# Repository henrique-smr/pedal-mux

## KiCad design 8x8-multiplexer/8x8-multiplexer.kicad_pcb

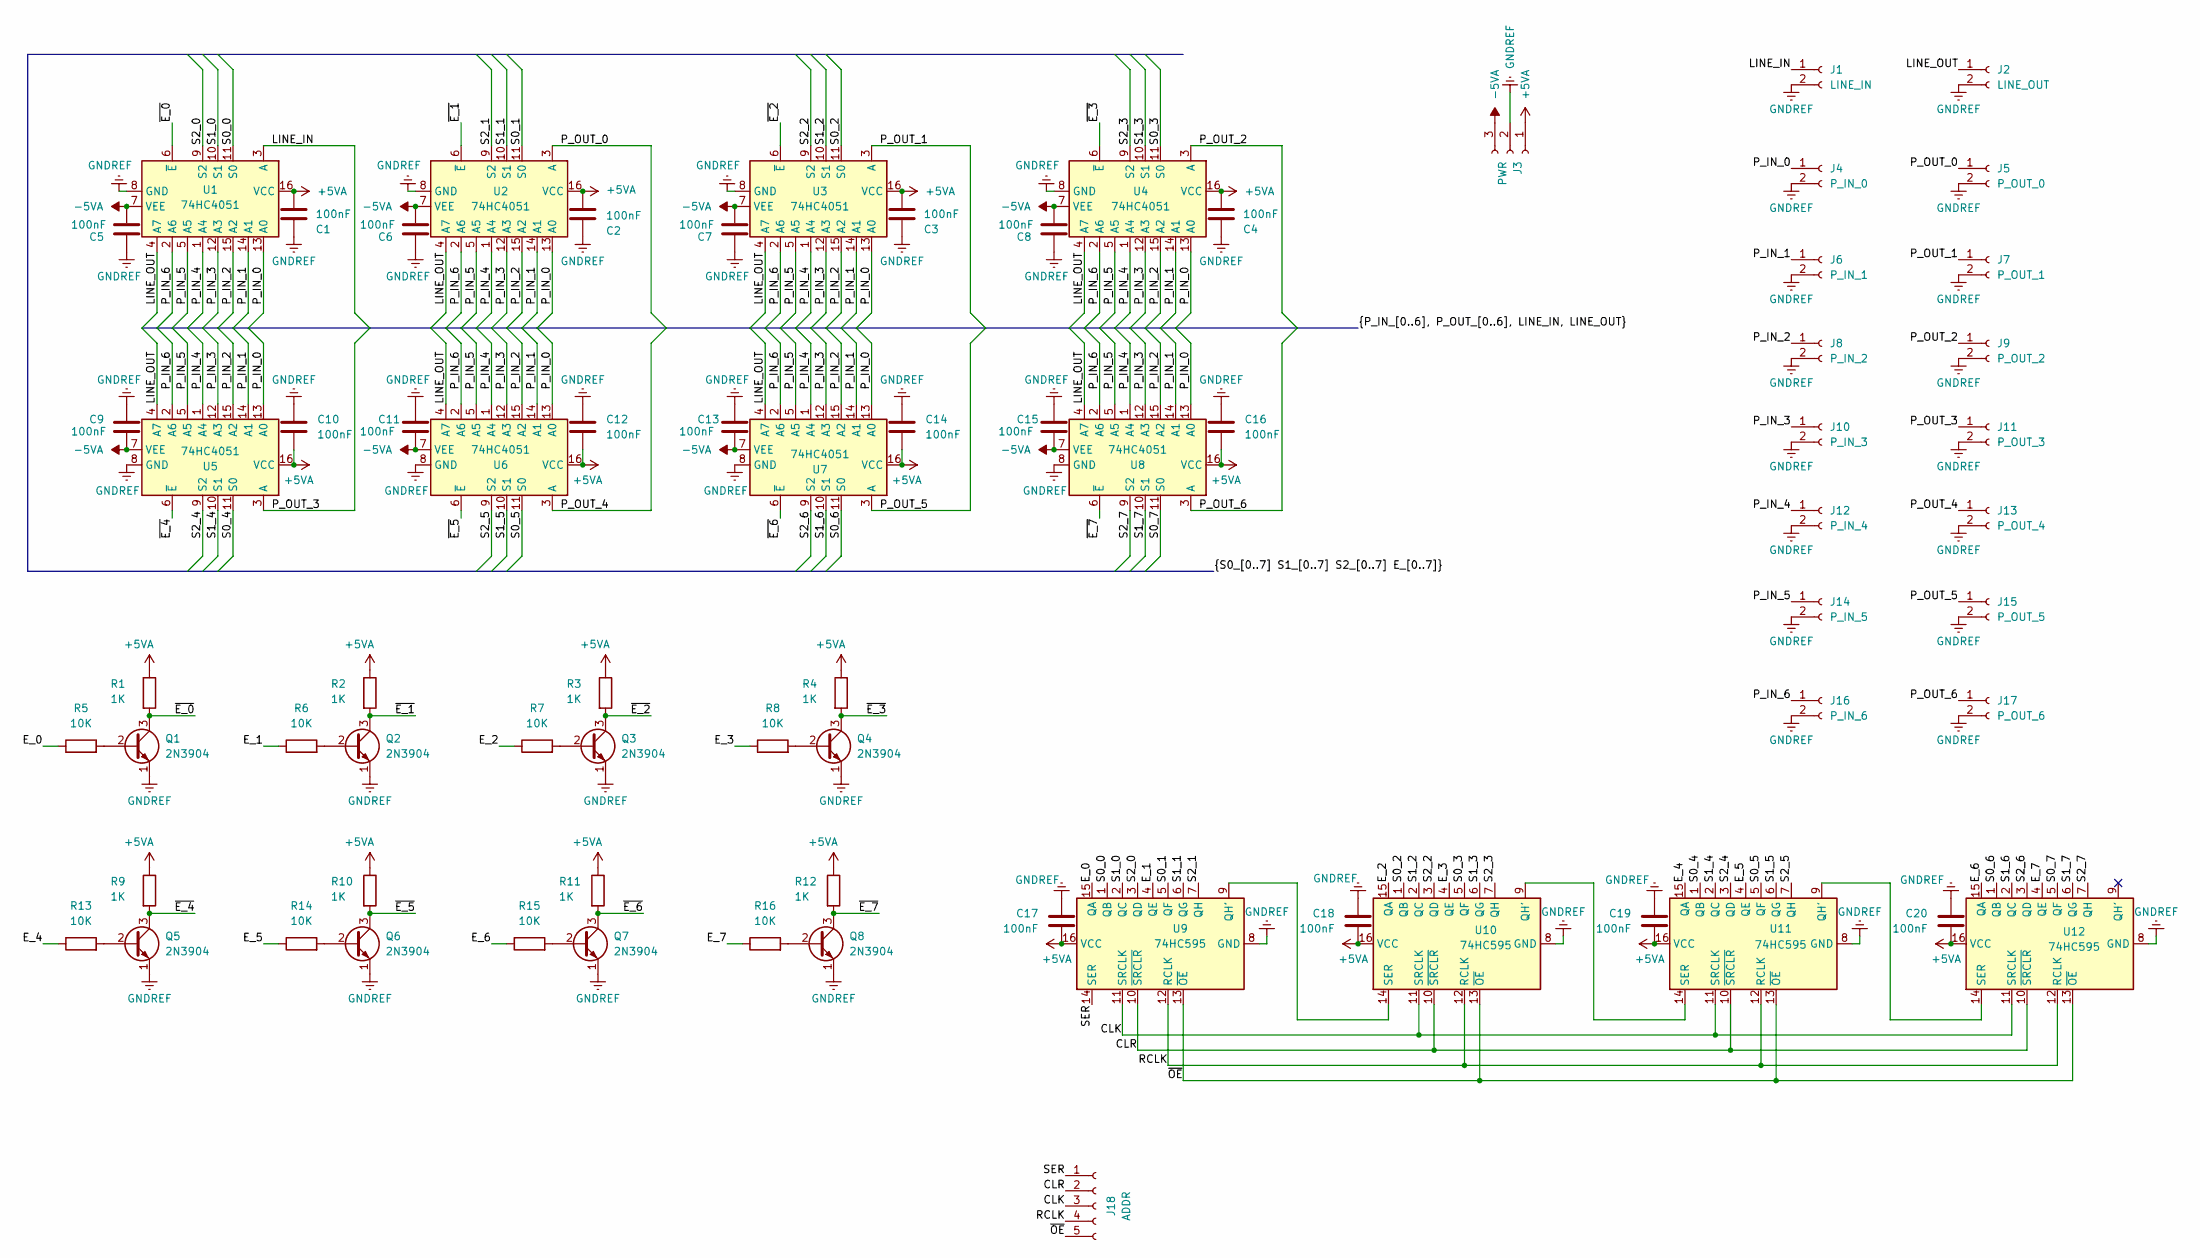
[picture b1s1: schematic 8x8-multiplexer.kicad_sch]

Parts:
C1, C2, C3, C4, C5, C6, C7, C8, C9, C10, C11, C12, C13, C14, C15, C16, C17, C18, C19, C20: 100nF; C_Disc_D4.3mm_W1.9mm_P5.00mm
J1: LINE_IN; PinSocket_1x02_P2.54mm_Vertical
J2: LINE_OUT; PinSocket_1x02_P2.54mm_Vertical
J3: PWR; PinSocket_1x03_P2.54mm_Vertical
J4: P_IN_0; PinSocket_1x02_P2.54mm_Vertical
J5: P_OUT_0; PinSocket_1x02_P2.54mm_Vertical
J6: P_IN_1; PinSocket_1x02_P2.54mm_Vertical
J7: P_OUT_1; PinSocket_1x02_P2.54mm_Vertical
J8: P_IN_2; PinSocket_1x02_P2.54mm_Vertical
J9: P_OUT_2; PinSocket_1x02_P2.54mm_Vertical
J10: P_IN_3; PinSocket_1x02_P2.54mm_Vertical
J11: P_OUT_3; PinSocket_1x02_P2.54mm_Vertical
J12: P_IN_4; PinSocket_1x02_P2.54mm_Vertical
J13: P_OUT_4; PinSocket_1x02_P2.54mm_Vertical
J14: P_IN_5; PinSocket_1x02_P2.54mm_Vertical
J15: P_OUT_5; PinSocket_1x02_P2.54mm_Vertical
J16: P_IN_6; PinSocket_1x02_P2.54mm_Vertical
J17: P_OUT_6; PinSocket_1x02_P2.54mm_Vertical
J18: ADDR; PinSocket_1x05_P2.54mm_Vertical
Q1, Q2, Q3, Q4, Q5, Q6, Q7, Q8: 2N3904; TO-92_Inline_Wide
R1, R2, R3, R4, R9, R10, R11, R12: 1K; R_Axial_DIN0207_L6.3mm_D2.5mm_P7.62mm_Horizontal
R5, R6, R7, R8, R13, R14, R15, R16: 10K; R_Axial_DIN0207_L6.3mm_D2.5mm_P7.62mm_Horizontal
U1, U2, U3, U4, U5, U6, U7, U8: 74HC4051; DIP-16_W7.62mm_LongPads
U9, U10, U11, U12: 74HC595; DIP-16_W7.62mm_LongPads

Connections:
+5VA: C1.2, C2.2, C3.2, C4.2, C10.2, C12.2, C14.2, C16.2, C17.2, C18.2, C19.2, C20.2, J3.1, R1.1, R2.1, R3.1, R4.1, R9.1, R10.1, R11.1, R12.1, U1.16 (VCC), U2.16 (VCC), U3.16 (VCC), U4.16 (VCC), U5.16 (VCC), U6.16 (VCC), U7.16 (VCC), U8.16 (VCC), U9.16 (VCC), U10.16 (VCC), U11.16 (VCC), U12.16 (VCC)
-5VA: C5.2, C6.2, C7.2, C8.2, C9.2, C11.2, C13.2, C15.2, J3.3, U1.7 (VEE), U2.7 (VEE), U3.7 (VEE), U4.7 (VEE), U5.7 (VEE), U6.7 (VEE), U7.7 (VEE), U8.7 (VEE)
/CLK: J18.3, U9.11 (SRCLK), U10.11 (SRCLK), U11.11 (SRCLK), U12.11 (SRCLK)
/CLR: J18.2, U9.10 (~SRCLR), U10.10 (~SRCLR), U11.10 (~SRCLR), U12.10 (~SRCLR)
/E_0: R5.1, U9.15 (QA)
/E_1: R6.1, U9.4 (QE)
/E_2: R7.1, U10.15 (QA)
/E_3: R8.1, U10.4 (QE)
/E_4: R13.1, U11.15 (QA)
/E_5: R14.1, U11.4 (QE)
/E_6: R15.1, U12.15 (QA)
/E_7: R16.1, U12.4 (QE)
/LINE_IN: J1.1, U1.3 (A)
/LINE_OUT: J2.1, U1.4 (A7), U2.4 (A7), U3.4 (A7), U4.4 (A7), U5.4 (A7), U6.4 (A7), U7.4 (A7), U8.4 (A7)
/P_IN_0: J4.1, U1.13 (A0), U2.13 (A0), U3.13 (A0), U4.13 (A0), U5.13 (A0), U6.13 (A0), U7.13 (A0), U8.13 (A0)
/P_IN_1: J6.1, U1.14 (A1), U2.14 (A1), U3.14 (A1), U4.14 (A1), U5.14 (A1), U6.14 (A1), U7.14 (A1), U8.14 (A1)
/P_IN_2: J8.1, U1.15 (A2), U2.15 (A2), U3.15 (A2), U4.15 (A2), U5.15 (A2), U6.15 (A2), U7.15 (A2), U8.15 (A2)
/P_IN_3: J10.1, U1.12 (A3), U2.12 (A3), U3.12 (A3), U4.12 (A3), U5.12 (A3), U6.12 (A3), U7.12 (A3), U8.12 (A3)
/P_IN_4: J12.1, U1.1 (A4), U2.1 (A4), U3.1 (A4), U4.1 (A4), U5.1 (A4), U6.1 (A4), U7.1 (A4), U8.1 (A4)
/P_IN_5: J14.1, U1.5 (A5), U2.5 (A5), U3.5 (A5), U4.5 (A5), U5.5 (A5), U6.5 (A5), U7.5 (A5), U8.5 (A5)
/P_IN_6: J16.1, U1.2 (A6), U2.2 (A6), U3.2 (A6), U4.2 (A6), U5.2 (A6), U6.2 (A6), U7.2 (A6), U8.2 (A6)
/P_OUT_0: J5.1, U2.3 (A)
/P_OUT_1: J7.1, U3.3 (A)
/P_OUT_2: J9.1, U4.3 (A)
/P_OUT_3: J11.1, U5.3 (A)
/P_OUT_4: J13.1, U6.3 (A)
/P_OUT_5: J15.1, U7.3 (A)
/P_OUT_6: J17.1, U8.3 (A)
/RCLK: J18.4, U9.12 (RCLK), U10.12 (RCLK), U11.12 (RCLK), U12.12 (RCLK)
/S0_0: U1.11 (S0), U9.1 (QB)
/S0_1: U2.11 (S0), U9.5 (QF)
/S0_2: U3.11 (S0), U10.1 (QB)
/S0_3: U4.11 (S0), U10.5 (QF)
/S0_4: U5.11 (S0), U11.1 (QB)
/S0_5: U6.11 (S0), U11.5 (QF)
/S0_6: U7.11 (S0), U12.1 (QB)
/S0_7: U8.11 (S0), U12.5 (QF)
/S1_0: U1.10 (S1), U9.2 (QC)
/S1_1: U2.10 (S1), U9.6 (QG)
/S1_2: U3.10 (S1), U10.2 (QC)
/S1_3: U4.10 (S1), U10.6 (QG)
/S1_4: U5.10 (S1), U11.2 (QC)
/S1_5: U6.10 (S1), U11.6 (QG)
/S1_6: U7.10 (S1), U12.2 (QC)
/S1_7: U8.10 (S1), U12.6 (QG)
/S2_0: U1.9 (S2), U9.3 (QD)
/S2_1: U2.9 (S2), U9.7 (QH)
/S2_2: U3.9 (S2), U10.3 (QD)
/S2_3: U4.9 (S2), U10.7 (QH)
/S2_4: U5.9 (S2), U11.3 (QD)
/S2_5: U6.9 (S2), U11.7 (QH)
/S2_6: U7.9 (S2), U12.3 (QD)
/S2_7: U8.9 (S2), U12.7 (QH)
/SER: J18.1, U9.14 (SER)
/~E_0: Q1.3 (C), R1.2, U1.6 (~E)
/~E_1: Q2.3 (C), R2.2, U2.6 (~E)
/~E_2: Q3.3 (C), R3.2, U3.6 (~E)
/~E_3: Q4.3 (C), R4.2, U4.6 (~E)
/~E_4: Q5.3 (C), R9.2, U5.6 (~E)
/~E_5: Q6.3 (C), R10.2, U6.6 (~E)
/~E_6: Q7.3 (C), R11.2, U7.6 (~E)
/~E_7: Q8.3 (C), R12.2, U8.6 (~E)
/~OE: J18.5, U9.13 (~OE), U10.13 (~OE), U11.13 (~OE), U12.13 (~OE)
GNDREF: C1.1, C2.1, C3.1, C4.1, C5.1, C6.1, C7.1, C8.1, C9.1, C10.1, C11.1, C12.1, C13.1, C14.1, C15.1, C16.1, C17.1, C18.1, C19.1, C20.1, J1.2, J2.2, J3.2, J4.2, J5.2, J6.2, J7.2, J8.2, J9.2, J10.2, J11.2, J12.2, J13.2, J14.2, J15.2, J16.2, J17.2, Q1.1 (E), Q2.1 (E), Q3.1 (E), Q4.1 (E), Q5.1 (E), Q6.1 (E), Q7.1 (E), Q8.1 (E), U1.8 (GND), U2.8 (GND), U3.8 (GND), U4.8 (GND), U5.8 (GND), U6.8 (GND), U7.8 (GND), U8.8 (GND), U9.8 (GND), U10.8 (GND), U11.8 (GND), U12.8 (GND)
unnamed: Q1.2 (B), R5.2
unnamed: Q2.2 (B), R6.2
unnamed: Q3.2 (B), R7.2
unnamed: Q4.2 (B), R8.2
unnamed: Q5.2 (B), R13.2
unnamed: Q6.2 (B), R14.2
unnamed: Q7.2 (B), R15.2
unnamed: Q8.2 (B), R16.2
unnamed: U10.9 (QH'), U11.14 (SER)
unnamed: U9.9 (QH'), U10.14 (SER)
unnamed: U11.9 (QH'), U12.14 (SER)

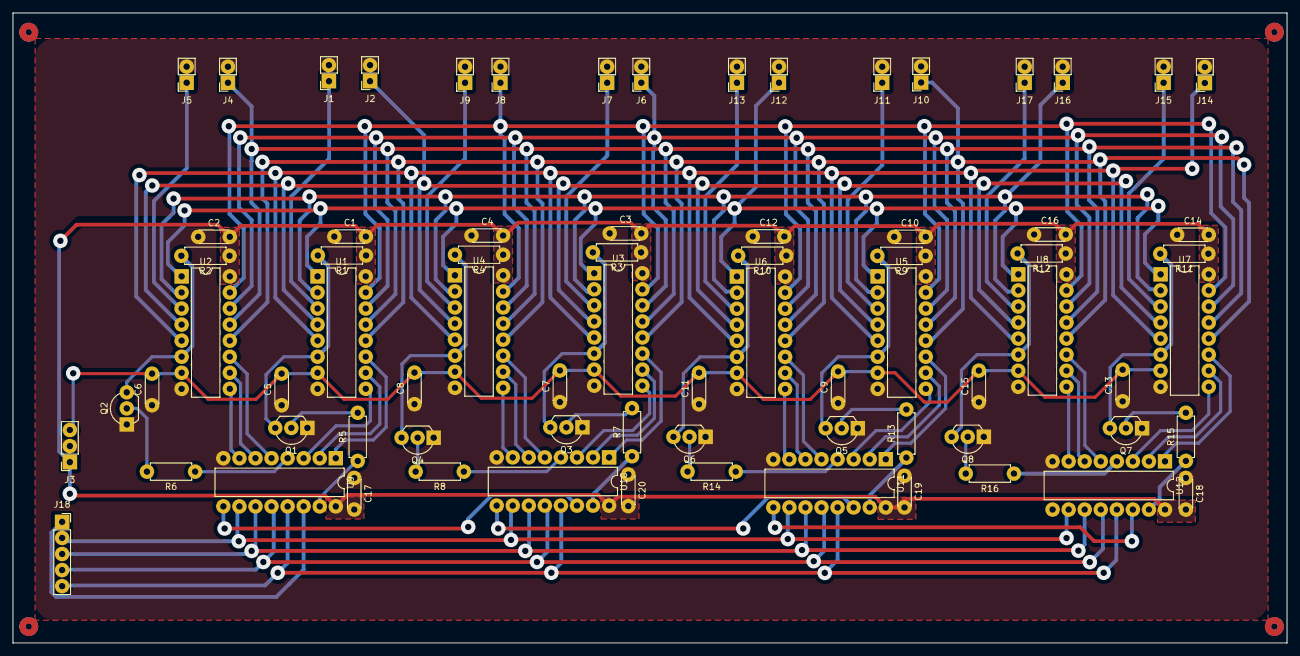
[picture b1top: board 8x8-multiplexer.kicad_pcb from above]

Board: 2 copper layers, 201.5 x 99.6 mm, 74 parts (0 on the bottom side), 75 nets.

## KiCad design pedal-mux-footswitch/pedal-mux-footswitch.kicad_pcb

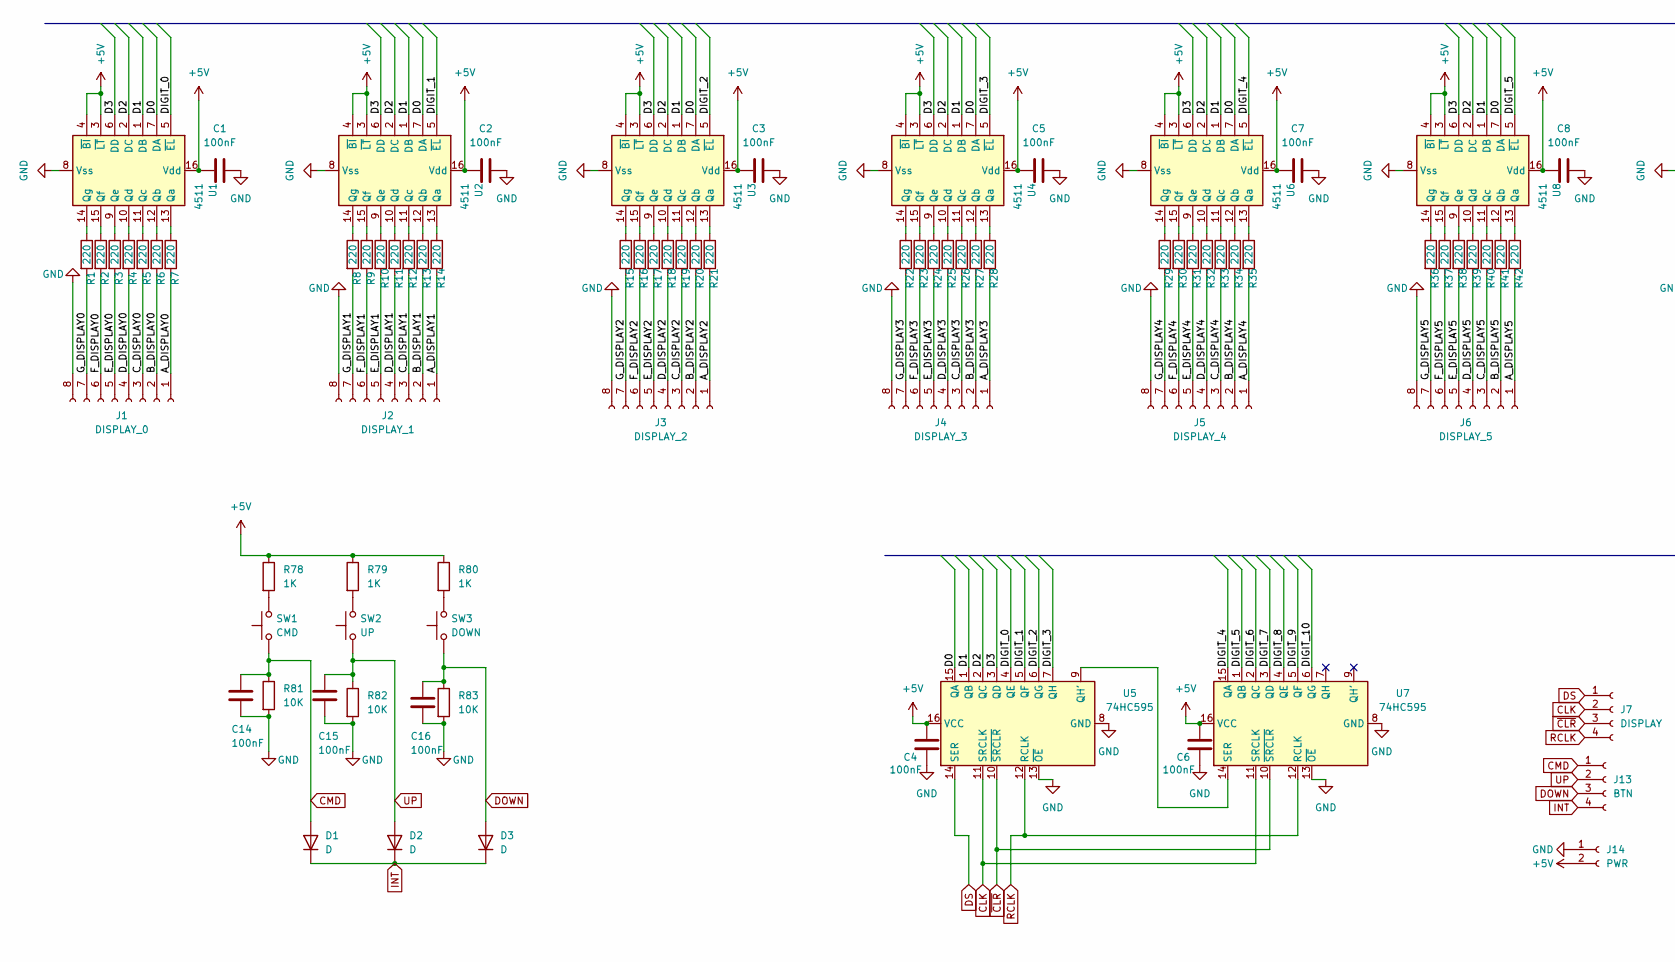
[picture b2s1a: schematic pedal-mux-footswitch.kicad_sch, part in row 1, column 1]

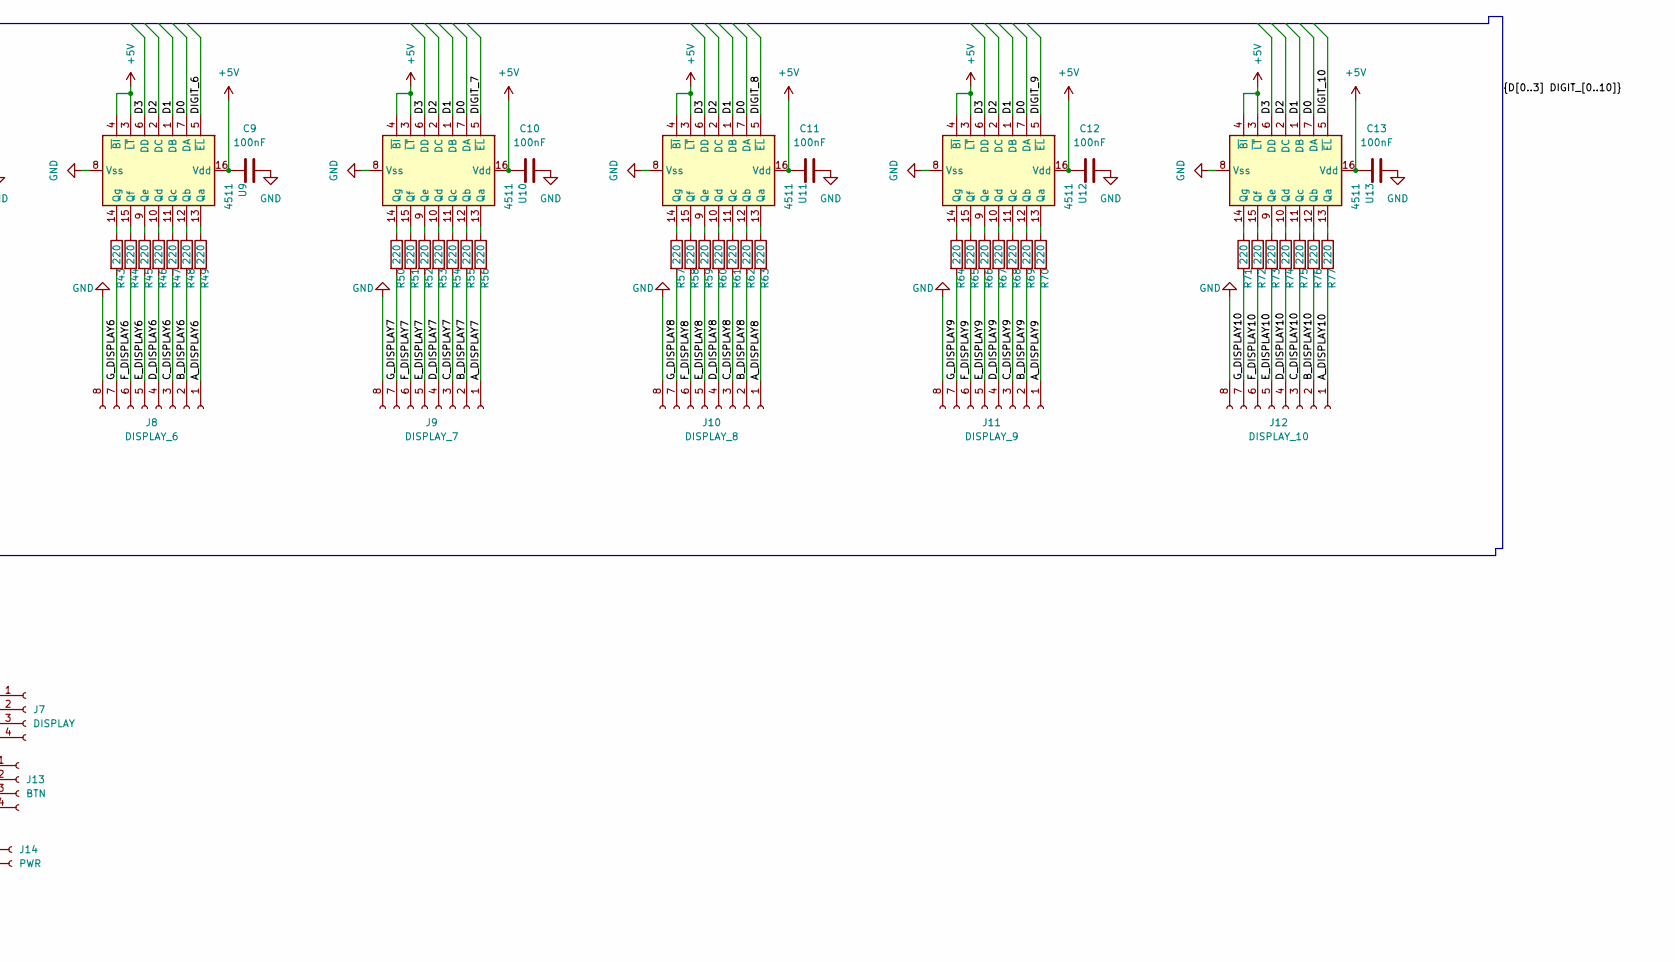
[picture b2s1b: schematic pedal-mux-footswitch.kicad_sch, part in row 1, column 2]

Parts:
C1, C2, C3, C4, C5, C6, C7, C8, C9, C10, C11, C12, C13, C14, C15, C16: 100nF; C_Disc_D5.0mm_W2.5mm_P2.50mm
D1, D2, D3: D; D_DO-41_SOD81_P10.16mm_Horizontal
J1: DISPLAY_0; PinSocket_1x08_P2.54mm_Vertical
J2: DISPLAY_1; PinSocket_1x08_P2.54mm_Vertical
J3: DISPLAY_2; PinSocket_1x08_P2.54mm_Vertical
J4: DISPLAY_3; PinSocket_1x08_P2.54mm_Vertical
J5: DISPLAY_4; PinSocket_1x08_P2.54mm_Vertical
J6: DISPLAY_5; PinSocket_1x08_P2.54mm_Vertical
J7: DISPLAY; PinSocket_1x04_P2.54mm_Vertical
J8: DISPLAY_6; PinSocket_1x08_P2.54mm_Vertical
J9: DISPLAY_7; PinSocket_1x08_P2.54mm_Vertical
J10: DISPLAY_8; PinSocket_1x08_P2.54mm_Vertical
J11: DISPLAY_9; PinSocket_1x08_P2.54mm_Vertical
J12: DISPLAY_10; PinSocket_1x08_P2.54mm_Vertical
J13: BTN; PinSocket_1x04_P2.54mm_Vertical
J14: PWR; PinSocket_1x02_P2.54mm_Vertical
R1, R2, R3, R4, R5, R6, R7, R8, R9, R10, R11, R12, R13, R14, R15, R16, R17, R18, R19, R20, R21, R22, R23, R24, R25, R26, R27, R28, R29, R30, R31, R32, R33, R34, R35, R36, R37, R38, R39, R40, R41, R42, R43, R44, R45, R46, R47, R48, R49, R50, R51, R52, R53, R54, R55, R56, R57, R58, R59, R60, R61, R62, R63, R64, R65, R66, R67, R68, R69, R70, R71, R72, R73, R74, R75, R76, R77: 220; R_Axial_DIN0204_L3.6mm_D1.6mm_P2.54mm_Vertical
R78, R79, R80: 1K; R_Axial_DIN0207_L6.3mm_D2.5mm_P2.54mm_Vertical
R81, R82, R83: 10K; R_Axial_DIN0207_L6.3mm_D2.5mm_P2.54mm_Vertical
SW1: CMD; PinSocket_1x02_P2.54mm_Vertical
SW2: UP; PinSocket_1x02_P2.54mm_Vertical
SW3: DOWN; PinSocket_1x02_P2.54mm_Vertical
U1, U2, U3, U4, U6, U8, U9, U10, U11, U12, U13: 4511; DIP-16_W7.62mm
U5, U7: 74HC595; DIP-16_W7.62mm

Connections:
+5V: C1.1, C2.1, C3.1, C4.1, C5.1, C6.1, C7.1, C8.1, C9.1, C10.1, C11.1, C12.1, C13.1, J14.2, R78.1, R79.1, R80.1, U1.3 (~LT), U1.4 (~BI), U1.16 (Vdd), U2.3 (~LT), U2.4 (~BI), U2.16 (Vdd), U3.3 (~LT), U3.4 (~BI), U3.16 (Vdd), U4.3 (~LT), U4.4 (~BI), U4.16 (Vdd), U5.16 (VCC), U6.3 (~LT), U6.4 (~BI), U6.16 (Vdd), U7.16 (VCC), U8.3 (~LT), U8.4 (~BI), U8.16 (Vdd), U9.3 (~LT), U9.4 (~BI), U9.16 (Vdd), U10.3 (~LT), U10.4 (~BI), U10.16 (Vdd), U11.3 (~LT), U11.4 (~BI), U11.16 (Vdd), U12.3 (~LT), U12.4 (~BI), U12.16 (Vdd), U13.3 (~LT), U13.4 (~BI), U13.16 (Vdd)
/A_DISPLAY0: J1.1, R7.2
/A_DISPLAY1: J2.1, R14.2
/A_DISPLAY2: J3.1, R21.2
/A_DISPLAY3: J4.1, R28.2
/A_DISPLAY4: J5.1, R35.2
/A_DISPLAY5: J6.1, R42.2
/A_DISPLAY6: J8.1, R49.2
/A_DISPLAY7: J9.1, R56.2
/A_DISPLAY8: J10.1, R63.2
/A_DISPLAY9: J11.1, R70.2
/A_DISPLAY10: J12.1, R77.2
/B_DISPLAY0: J1.2, R6.2
/B_DISPLAY1: J2.2, R13.2
/B_DISPLAY2: J3.2, R20.2
/B_DISPLAY3: J4.2, R27.2
/B_DISPLAY4: J5.2, R34.2
/B_DISPLAY5: J6.2, R41.2
/B_DISPLAY6: J8.2, R48.2
/B_DISPLAY7: J9.2, R55.2
/B_DISPLAY8: J10.2, R62.2
/B_DISPLAY9: J11.2, R69.2
/B_DISPLAY10: J12.2, R76.2
/C_DISPLAY0: J1.3, R5.2
/C_DISPLAY1: J2.3, R12.2
/C_DISPLAY2: J3.3, R19.2
/C_DISPLAY3: J4.3, R26.2
/C_DISPLAY4: J5.3, R33.2
/C_DISPLAY5: J6.3, R40.2
/C_DISPLAY6: J8.3, R47.2
/C_DISPLAY7: J9.3, R54.2
/C_DISPLAY8: J10.3, R61.2
/C_DISPLAY9: J11.3, R68.2
/C_DISPLAY10: J12.3, R75.2
/D0: U1.7 (DA), U2.7 (DA), U3.7 (DA), U4.7 (DA), U5.15 (QA), U6.7 (DA), U8.7 (DA), U9.7 (DA), U10.7 (DA), U11.7 (DA), U12.7 (DA), U13.7 (DA)
/D1: U1.1 (DB), U2.1 (DB), U3.1 (DB), U4.1 (DB), U5.1 (QB), U6.1 (DB), U8.1 (DB), U9.1 (DB), U10.1 (DB), U11.1 (DB), U12.1 (DB), U13.1 (DB)
/D2: U1.2 (DC), U2.2 (DC), U3.2 (DC), U4.2 (DC), U5.2 (QC), U6.2 (DC), U8.2 (DC), U9.2 (DC), U10.2 (DC), U11.2 (DC), U12.2 (DC), U13.2 (DC)
/D3: U1.6 (DD), U2.6 (DD), U3.6 (DD), U4.6 (DD), U5.3 (QD), U6.6 (DD), U8.6 (DD), U9.6 (DD), U10.6 (DD), U11.6 (DD), U12.6 (DD), U13.6 (DD)
/DIGIT_0: U1.5 (~EL), U5.4 (QE)
/DIGIT_1: U2.5 (~EL), U5.5 (QF)
/DIGIT_2: U3.5 (~EL), U5.6 (QG)
/DIGIT_3: U4.5 (~EL), U5.7 (QH)
/DIGIT_4: U6.5 (~EL), U7.15 (QA)
/DIGIT_5: U7.1 (QB), U8.5 (~EL)
/DIGIT_6: U7.2 (QC), U9.5 (~EL)
/DIGIT_7: U7.3 (QD), U10.5 (~EL)
/DIGIT_8: U7.4 (QE), U11.5 (~EL)
/DIGIT_9: U7.5 (QF), U12.5 (~EL)
/DIGIT_10: U7.6 (QG), U13.5 (~EL)
/D_DISPLAY0: J1.4, R4.2
/D_DISPLAY1: J2.4, R11.2
/D_DISPLAY2: J3.4, R18.2
/D_DISPLAY3: J4.4, R25.2
/D_DISPLAY4: J5.4, R32.2
/D_DISPLAY5: J6.4, R39.2
/D_DISPLAY6: J8.4, R46.2
/D_DISPLAY7: J9.4, R53.2
/D_DISPLAY8: J10.4, R60.2
/D_DISPLAY9: J11.4, R67.2
/D_DISPLAY10: J12.4, R74.2
/E_DISPLAY0: J1.5, R3.2
/E_DISPLAY1: J2.5, R10.2
/E_DISPLAY2: J3.5, R17.2
/E_DISPLAY3: J4.5, R24.2
/E_DISPLAY4: J5.5, R31.2
/E_DISPLAY5: J6.5, R38.2
/E_DISPLAY6: J8.5, R45.2
/E_DISPLAY7: J9.5, R52.2
/E_DISPLAY8: J10.5, R59.2
/E_DISPLAY9: J11.5, R66.2
/E_DISPLAY10: J12.5, R73.2
/F_DISPLAY0: J1.6, R2.2
/F_DISPLAY1: J2.6, R9.2
/F_DISPLAY2: J3.6, R16.2
/F_DISPLAY3: J4.6, R23.2
/F_DISPLAY4: J5.6, R30.2
/F_DISPLAY5: J6.6, R37.2
/F_DISPLAY6: J8.6, R44.2
/F_DISPLAY7: J9.6, R51.2
/F_DISPLAY8: J10.6, R58.2
/F_DISPLAY9: J11.6, R65.2
/F_DISPLAY10: J12.6, R72.2
/G_DISPLAY0: J1.7, R1.2
/G_DISPLAY1: J2.7, R8.2
/G_DISPLAY2: J3.7, R15.2
/G_DISPLAY3: J4.7, R22.2
/G_DISPLAY4: J5.7, R29.2
/G_DISPLAY5: J6.7, R36.2
/G_DISPLAY6: J8.7, R43.2
/G_DISPLAY7: J9.7, R50.2
/G_DISPLAY8: J10.7, R57.2
/G_DISPLAY9: J11.7, R64.2
/G_DISPLAY10: J12.7, R71.2
CLK: J7.2, U5.11 (SRCLK), U7.11 (SRCLK)
CMD: C14.1, D1.2 (A), J13.1, R81.1, SW1.1
DOWN: C16.1, D3.2 (A), J13.3, R83.1, SW3.1
DS: J7.1, U5.14 (SER)
GND: C1.2, C2.2, C3.2, C4.2, C5.2, C6.2, C7.2, C8.2, C9.2, C10.2, C11.2, C12.2, C13.2, C14.2, C15.2, C16.2, J1.8, J2.8, J3.8, J4.8, J5.8, J6.8, J8.8, J9.8, J10.8, J11.8, J12.8, J14.1, R81.2, R82.2, R83.2, U1.8 (Vss), U2.8 (Vss), U3.8 (Vss), U4.8 (Vss), U5.8 (GND), U5.13 (~OE), U6.8 (Vss), U7.8 (GND), U7.13 (~OE), U8.8 (Vss), U9.8 (Vss), U10.8 (Vss), U11.8 (Vss), U12.8 (Vss), U13.8 (Vss)
INT: D1.1 (K), D2.1 (K), D3.1 (K), J13.4
unnamed: R78.2, SW1.2
unnamed: R79.2, SW2.2
unnamed: R80.2, SW3.2
unnamed: R7.1, U1.13 (Qa)
unnamed: R6.1, U1.12 (Qb)
unnamed: R5.1, U1.11 (Qc)
unnamed: R4.1, U1.10 (Qd)
unnamed: R3.1, U1.9 (Qe)
unnamed: R2.1, U1.15 (Qf)
unnamed: R1.1, U1.14 (Qg)
unnamed: R14.1, U2.13 (Qa)
unnamed: R13.1, U2.12 (Qb)
unnamed: R12.1, U2.11 (Qc)
unnamed: R11.1, U2.10 (Qd)
unnamed: R10.1, U2.9 (Qe)
unnamed: R9.1, U2.15 (Qf)
unnamed: R8.1, U2.14 (Qg)
unnamed: R21.1, U3.13 (Qa)
unnamed: R20.1, U3.12 (Qb)
unnamed: R19.1, U3.11 (Qc)
unnamed: R18.1, U3.10 (Qd)
unnamed: R17.1, U3.9 (Qe)
unnamed: R16.1, U3.15 (Qf)
unnamed: R15.1, U3.14 (Qg)
unnamed: R28.1, U4.13 (Qa)
unnamed: R27.1, U4.12 (Qb)
unnamed: R26.1, U4.11 (Qc)
unnamed: R25.1, U4.10 (Qd)
unnamed: R24.1, U4.9 (Qe)
unnamed: R23.1, U4.15 (Qf)
unnamed: R22.1, U4.14 (Qg)
unnamed: U5.9 (QH'), U7.14 (SER)
unnamed: R35.1, U6.13 (Qa)
unnamed: R34.1, U6.12 (Qb)
unnamed: R33.1, U6.11 (Qc)
unnamed: R32.1, U6.10 (Qd)
unnamed: R31.1, U6.9 (Qe)
unnamed: R30.1, U6.15 (Qf)
unnamed: R29.1, U6.14 (Qg)
unnamed: R42.1, U8.13 (Qa)
unnamed: R41.1, U8.12 (Qb)
unnamed: R40.1, U8.11 (Qc)
unnamed: R39.1, U8.10 (Qd)
unnamed: R38.1, U8.9 (Qe)
unnamed: R37.1, U8.15 (Qf)
unnamed: R36.1, U8.14 (Qg)
unnamed: R49.1, U9.13 (Qa)
unnamed: R48.1, U9.12 (Qb)
unnamed: R47.1, U9.11 (Qc)
unnamed: R46.1, U9.10 (Qd)
unnamed: R45.1, U9.9 (Qe)
unnamed: R44.1, U9.15 (Qf)
unnamed: R43.1, U9.14 (Qg)
unnamed: R56.1, U10.13 (Qa)
unnamed: R55.1, U10.12 (Qb)
unnamed: R54.1, U10.11 (Qc)
unnamed: R53.1, U10.10 (Qd)
unnamed: R52.1, U10.9 (Qe)
unnamed: R51.1, U10.15 (Qf)
unnamed: R50.1, U10.14 (Qg)
unnamed: R63.1, U11.13 (Qa)
unnamed: R62.1, U11.12 (Qb)
unnamed: R61.1, U11.11 (Qc)
unnamed: R60.1, U11.10 (Qd)
unnamed: R59.1, U11.9 (Qe)
unnamed: R58.1, U11.15 (Qf)
unnamed: R57.1, U11.14 (Qg)
unnamed: R70.1, U12.13 (Qa)
unnamed: R69.1, U12.12 (Qb)
unnamed: R68.1, U12.11 (Qc)
unnamed: R67.1, U12.10 (Qd)
unnamed: R66.1, U12.9 (Qe)
unnamed: R65.1, U12.15 (Qf)
unnamed: R64.1, U12.14 (Qg)
unnamed: R77.1, U13.13 (Qa)
unnamed: R76.1, U13.12 (Qb)
unnamed: R75.1, U13.11 (Qc)
unnamed: R74.1, U13.10 (Qd)
unnamed: R73.1, U13.9 (Qe)
unnamed: R72.1, U13.15 (Qf)
unnamed: R71.1, U13.14 (Qg)
RCLK: J7.4, U5.12 (RCLK), U7.12 (RCLK)
UP: C15.1, D2.2 (A), J13.2, R82.1, SW2.1
~CLR: J7.3, U5.10 (~SRCLR), U7.10 (~SRCLR)

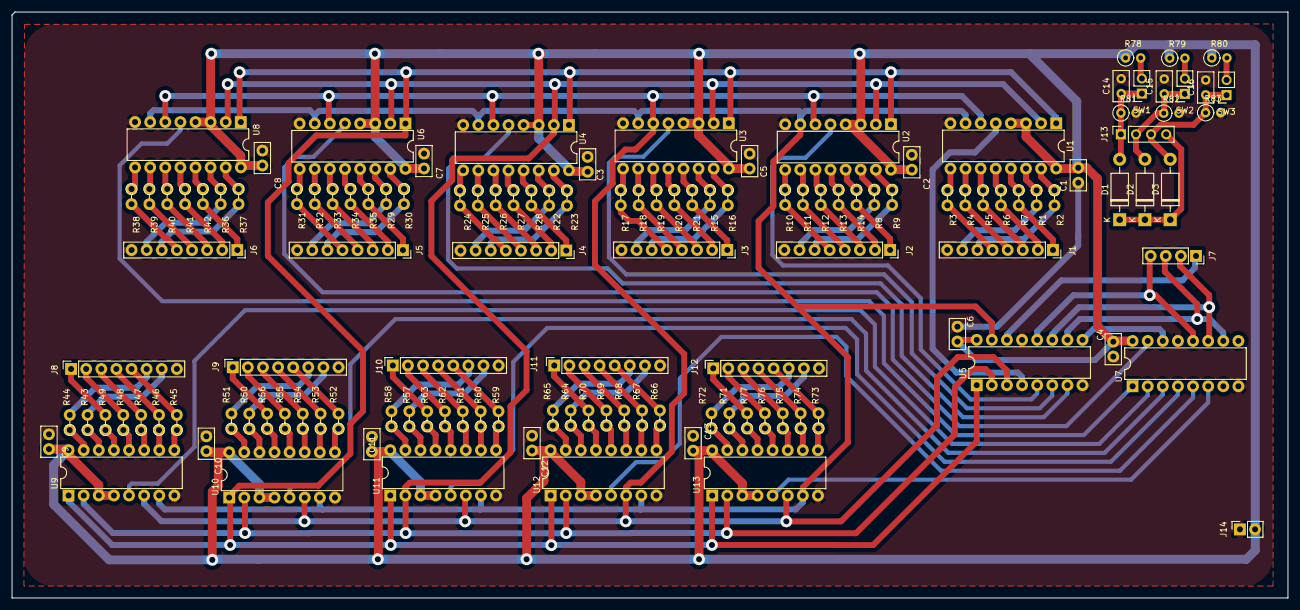
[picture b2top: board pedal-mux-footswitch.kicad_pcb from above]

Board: 2 copper layers, 214.5 x 98.5 mm, 132 parts (0 on the bottom side), 183 nets.
